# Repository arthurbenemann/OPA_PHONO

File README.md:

# OPA_PHONO

.jpg)

## RIAA filter Simulation
Overall response with (blue) and without(green) cartridge model:

RIAA Filter deviation assuming 2% capacitors and 1% resistors

## Mechanical Enclosure

### Hammond case
The CAD model is avaliable in Fusion360 at: https://a360.co/32rnA34.  I may design a faceplate PCB with graphics, but in the meantime the Hammond 1544L80 enclosure can be milled acording to the drawings at [OPA_PHONO_FACEPLATE.pdf](/Enclosure/OPA_PHONO_FACEPLATE.pdf). A compatible drawing with slighly larger holes, but more avaliable sizes is on the bottom drawing.

### 3D printed case
Mell, has created a 3d printed case for his build. Files stored under [Enclosure-3dprint/](./Enclosure-3dprint/)

## Measurements

**SN01** deviation from RIAA curve, based on measurements [SN01_REW.mdat](Measurements/SN01_REW.mdat). Note very close to noise floor at 15kHz, 60Hz hum and harmonics distorting measurement, low frequency behavior from testing equipment.

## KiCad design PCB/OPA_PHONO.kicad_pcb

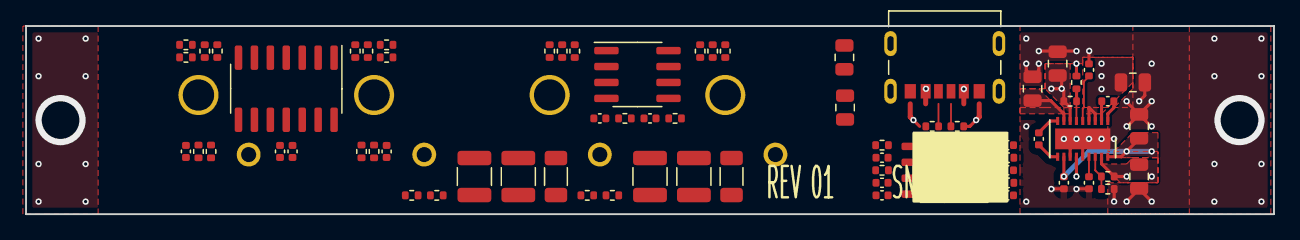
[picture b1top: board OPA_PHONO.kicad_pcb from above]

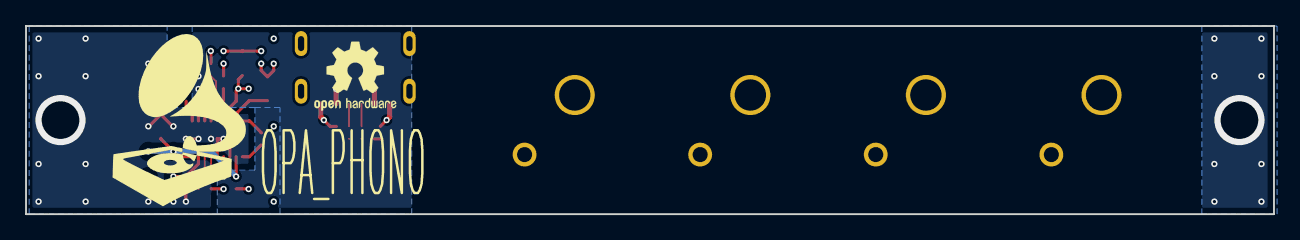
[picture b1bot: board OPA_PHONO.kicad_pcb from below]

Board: 4 copper layers, 99.5 x 15.0 mm, 71 parts (2 on the bottom side), 44 nets.

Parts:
C1, C7: NP; C_0402_1005Metric
C2, C3, C8, C9: 68n; C_1210_3225Metric
C4, C10: 47n; C_1206_3216Metric
C5, C6, C11, C12, C13, C14, C16, C17, C18, C19, C20, C21, C22, C29, C30: 1u; C_0402_1005Metric
C15, C23, C24, C25, C26, C27, C28: 10u; C_0805_2012Metric
J1, J2: RCJ-21XX
J3: UJC-HP-3-SMT-TR; CUI_UJC-HP-3-SMT-TR
R1, R9, R10, R11, R13, R21, R22, R23: 47k; R_0402_1005Metric
R2, R3, R4, R7, R14, R15, R16, R18, R19, R31, R32, R33: 16k; R_0402_1005Metric
R5, R17: 2.32k; R_0402_1005Metric
R6, R8, R12, R20, R24, R34: 499R; R_0402_1005Metric
R25, R28: 20.5k; R_0402_1005Metric
R26, R27, R29, R30: 5.1k; R_0402_1005Metric
U1: OPA1644AxD; SOIC-14_3.9x8.7mm_P1.27mm
U2, U4: OPA1612AxD; SOIC-8_3.9x4.9mm_P1.27mm
U3: LTC3265xDHC; DFN-18-1EP_3x5mm_P0.5mm_EP1.66x4.4mm

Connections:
/CC1: J3.A5 (CC1), R30.1
/CC2: J3.B5 (CC2), R29.1
/LEFT/FB1N: R32.2, R33.1, R34.1, U1.2 (-)
/LEFT/FB1P: R14.2, R31.1, R34.2, U1.13 (-)
/LEFT/FB2: R6.2, R19.2, R21.2, U2.6 (-)
/LEFT/FBTRIM: C11.2, R22.2, U4.6 (-)
/LEFT/INN: C7.2, J1.3 (Barrel_terminal_X2), R13.1, U1.3 (+)
/LEFT/INP: C7.1, J1.4 (Center_terminal_X2), R13.2, U1.12 (+)
/LEFT/OUT1: R14.1, R16.2, U1.14
/LEFT/OUT1B: R31.2, R32.1, U1.1
/LEFT/OUT2: R19.1, R23.1, R24.1, U2.7
/LEFT/OUT_RC: C12.1, R23.2, U4.5 (+)
/LEFT/RIAA: C10.1, R16.1, R17.2, U2.5 (+)
/LEFT/RIAA_RC: C8.1, C9.1, R17.1
/LEFT/TRIM: C11.1, R21.1, U4.7
/OUT_L: J2.4 (Center_terminal_X2), R24.2
/OUT_R: J2.2 (Center_terminal_X1), R12.2
/POWER/+6V: C15.2, C19.2, C21.2, C27.2, C29.2, R25.1, U1.4 (V+), U2.8 (V+), U3.17 (LDOP), U4.8 (V+)
/POWER/-6V: C20.1, C22.1, C25.1, C28.1, C30.1, R28.2, U1.11 (V-), U2.4 (V-), U3.7 (LDON), U4.4 (V-)
/POWER/ADJN: R27.2, R28.1, U3.6 (ADJN)
/POWER/ADJP: R25.2, R26.1, U3.16 (ADJP)
/POWER/BYPN: C18.1, U3.5 (BYPN)
/POWER/BYPP: C17.2, U3.15 (BYPP)
/POWER/CBSTN: C16.2, U3.1 (CBSTN)
/POWER/CBSTP: C16.1, U3.2 (CBSTP)
/POWER/CINVN: C14.1, U3.9 (CINVN)
/POWER/CINVP: C14.2, U3.10 (CINVP)
/POWER/VIN: C23.2, J3.A9 (VBUS), J3.B9 (VBUS), U3.3 (VINP), U3.4 (ENN), U3.13 (ENP)
/POWER/VOUTN: C24.2, U3.8 (VOUTN)
/POWER/VOUTP: C13.2, C26.2, U3.11 (VINN), U3.18 (VOUTP)
/RIGHT/FB1N: R15.2, R18.1, R20.1, U1.6 (-)
/RIGHT/FB1P: R2.2, R3.1, R20.2, U1.9 (-)
/RIGHT/FB2: R7.2, R8.2, R9.2, U2.2 (-)
/RIGHT/FBTRIM: C5.2, R10.2, U4.2 (-)
/RIGHT/INN: C1.2, J1.1 (Barrel_terminal_X1), R1.1, U1.5 (+)
/RIGHT/INP: C1.1, J1.2 (Center_terminal_X1), R1.2, U1.10 (+)
/RIGHT/OUT1: R2.1, R4.2, U1.8
/RIGHT/OUT1B: R3.2, R15.1, U1.7
/RIGHT/OUT2: R7.1, R11.1, R12.1, U2.1
/RIGHT/OUT_RC: C6.1, R11.2, U4.3 (+)
/RIGHT/RIAA: C4.1, R4.1, R5.2, U2.3 (+)
/RIGHT/RIAA_RC: C2.1, C3.1, R5.1
/RIGHT/TRIM: C5.1, R9.1, U4.1
GND: C2.2, C3.2, C4.2, C6.2, C8.2, C9.2, C10.2, C12.2, C13.1, C15.1, C17.1, C18.2, C19.1, C20.2, C21.1, C22.2, C23.1, C24.1, C25.2, C26.1, C27.1, C28.2, C29.1, C30.2, J2.1 (Barrel_terminal_X1), J2.3 (Barrel_terminal_X2), J3.A12 (GND), J3.B12 (GND), R6.1, R8.1, R10.1, R18.2, R22.1, R26.2, R27.1, R29.2, R30.2, R33.2, U3.12 (RT), U3.14 (MODE), U3.19 (GND)

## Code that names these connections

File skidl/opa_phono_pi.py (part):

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    value="LTC3265EDHC",
    footprint="Package_DFN_QFN:DFN-18-1EP_3x5mm_P0.5mm_EP1.66x4.4mm",
    pins=[
        Pin(num=1,  name="CBSTN", func=PIN.PASSIVE),
        Pin(num=2,  name="CBSTP", func=PIN.PASSIVE),
        Pin(num=3,  name="VINP",  func=PIN.PWRIN),
        Pin(num=4,  name="ENN",   func=PIN.INPUT),
        Pin(num=5,  name="BYPN",  func=PIN.PASSIVE),
        Pin(num=6,  name="ADJN",  func=PIN.INPUT),
        Pin(num=7,  name="LDON",  func=PIN.PWROUT),
        Pin(num=8,  name="VOUTN", func=PIN.PWROUT),
        Pin(num=9,  name="CINVN", func=PIN.PASSIVE),
        Pin(num=10, name="CINVP", func=PIN.PASSIVE),
        Pin(num=11, name="VINN",  func=PIN.PWRIN),
        Pin(num=12, name="RT",    func=PIN.INPUT),
        Pin(num=13, name="ENP",   func=PIN.INPUT),
        Pin(num=14, name="MODE",  func=PIN.INPUT),
        Pin(num=15, name="BYPP",  func=PIN.PASSIVE),
        Pin(num=16, name="ADJP",  func=PIN.INPUT),
        Pin(num=17, name="LDOP",  func=PIN.PWROUT),
        Pin(num=18, name="VOUTP", func=PIN.PWROUT),
        Pin(num=19, name="GND",   func=PIN.PWRIN),  # exposed pad
    ],
)
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    audio_in  : single-ended input from RCA jack
    audio_out : line-level output to ADC anti-alias filter
    s1_*      : pin handles for first OPA1644 section (gain stage)
    s2_*      : pin handles for second OPA1644 section (RIAA stage)
    buf_*     : pin handles for OPA1612 section (output buffer)
    """
    # --- Stage 1: flat gain ---
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
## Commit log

2022-01-07 Data
2022-01-08 CHANGE POWER SUPPLY
2022-01-08 UPDATE GITIGNORE
2022-01-09 update layout
2022-01-09 add usb c connector
2022-01-09 Update component fields
2022-01-09 routed all nets
2022-01-12 Clean DRC
2022-01-13 simplify BOM
2022-01-13 Add graphics, simplify output resistor
2022-01-13 change output resistor to 499R
2022-01-14 Generate Gerbers
2022-01-14 Organize files
2022-01-22 add dxf for front pannel, and pcb file
2022-01-22 add milling pdf
2022-01-22 add images
2022-02-01 Add mesurements
2022-02-13 ADD ZAL4059 test data
2022-02-21 differential amp initial changes
2026-05-09 Add SKiDL representation of the schematic
    Mirrors the KiCad hierarchy (top + RIAA_PHONO x2 + POWER) as a single
    Python file with subcircuits for power() and riaa_channel(). Net names
    match the schematic labels (RIAA, RIAA_RC, FB1, FB2, TRIM, FBTRIM,
    OUT_RC, etc.) so the topology is readable side-by-side with the .kicad_sch.
    https://claude.ai/code/session_01Ao8ETc8Mtp3pa8jkRJiXuB
2026-05-09 Define custom symbols in pure SKiDL; fix LTC3265 / OPA1644 pinouts
    Move the project-specific parts (OPA1644, OPA1612, LTC3265, PJRAS2X1S01X,
    UJC-HP-3-SMT-TR, Housing) into skidl/parts.py as Part templates so the
    SKiDL design no longer needs lib_search_paths to point at the .kicad_sym.
    Surfacing the real pin definitions exposed two bugs in the previous
    commit that came from looking up symbols by lib path:
    * LTC3265 has VINP (3) + VINN (11) inputs (not a single VIN), and the
2026-05-09 Add SKiDL design adding Raspberry Pi ADC HAT to OPA_PHONO
    Describes the full board in SKiDL: existing RIAA preamp (OPA1644 +
    OPA1612, +-6V) plus a 40-pin Pi GPIO header, PCM1863 stereo ADC with
    anti-alias front end, and a 24C32 HAT-ID EEPROM. Power comes from the
    Pi: 5V feeds the LTC3265 charge pump for the analog rails, 3.3V powers
    the ADC digital side and EEPROM. Audio path: RCA -> preamp ->
    AC-couple/AA filter -> PCM1863 -> I2S to Pi (BCM18/19/20).
2026-05-09 Ignore Python __pycache__
2026-05-09 Make SKiDL design self-contained (no external KiCad libs needed)
    Define every part inline using SKiDL tool=SKIDL with explicit Pin lists:
    R/C templates, OPA1644, OPA1612, LTC3265 (pin map matches existing
    OPA_PHONO:LTC3265xDHC symbol), PCM1863, 24C32 EEPROM, 40-pin Pi GPIO
    header, and the Switchcraft PJRAS2X1S01X RCA jack. The script now
    generates a 321-component netlist with ERC clean and zero dependency on
    KICAD_SYMBOL_DIR. Also gitignore SKiDL build artifacts (*.net, *.erc,
2026-05-09 Tag parts with Manufacturer/MPN fields and add bom.py CSV generator
    PART_DB lookup table maps (template, value) -> (Manufacturer, MPN).
    Existing BOM values keep their original Yageo/Murata/Panasonic/TI/ADI/
    Switchcraft part numbers; new parts (PCM1863DBTR, 24LC32AT-I/SN, Wurth
    2x20 header, AA-filter and decoupling caps) get reasonable picks. Each
    template has a thin value-aware constructor wrapper that attaches the
    fields via part.fields[...] (kwargs/attribute paths don't propagate to
2026-05-09 Ignore generated skidl/*.bom.csv artifacts
